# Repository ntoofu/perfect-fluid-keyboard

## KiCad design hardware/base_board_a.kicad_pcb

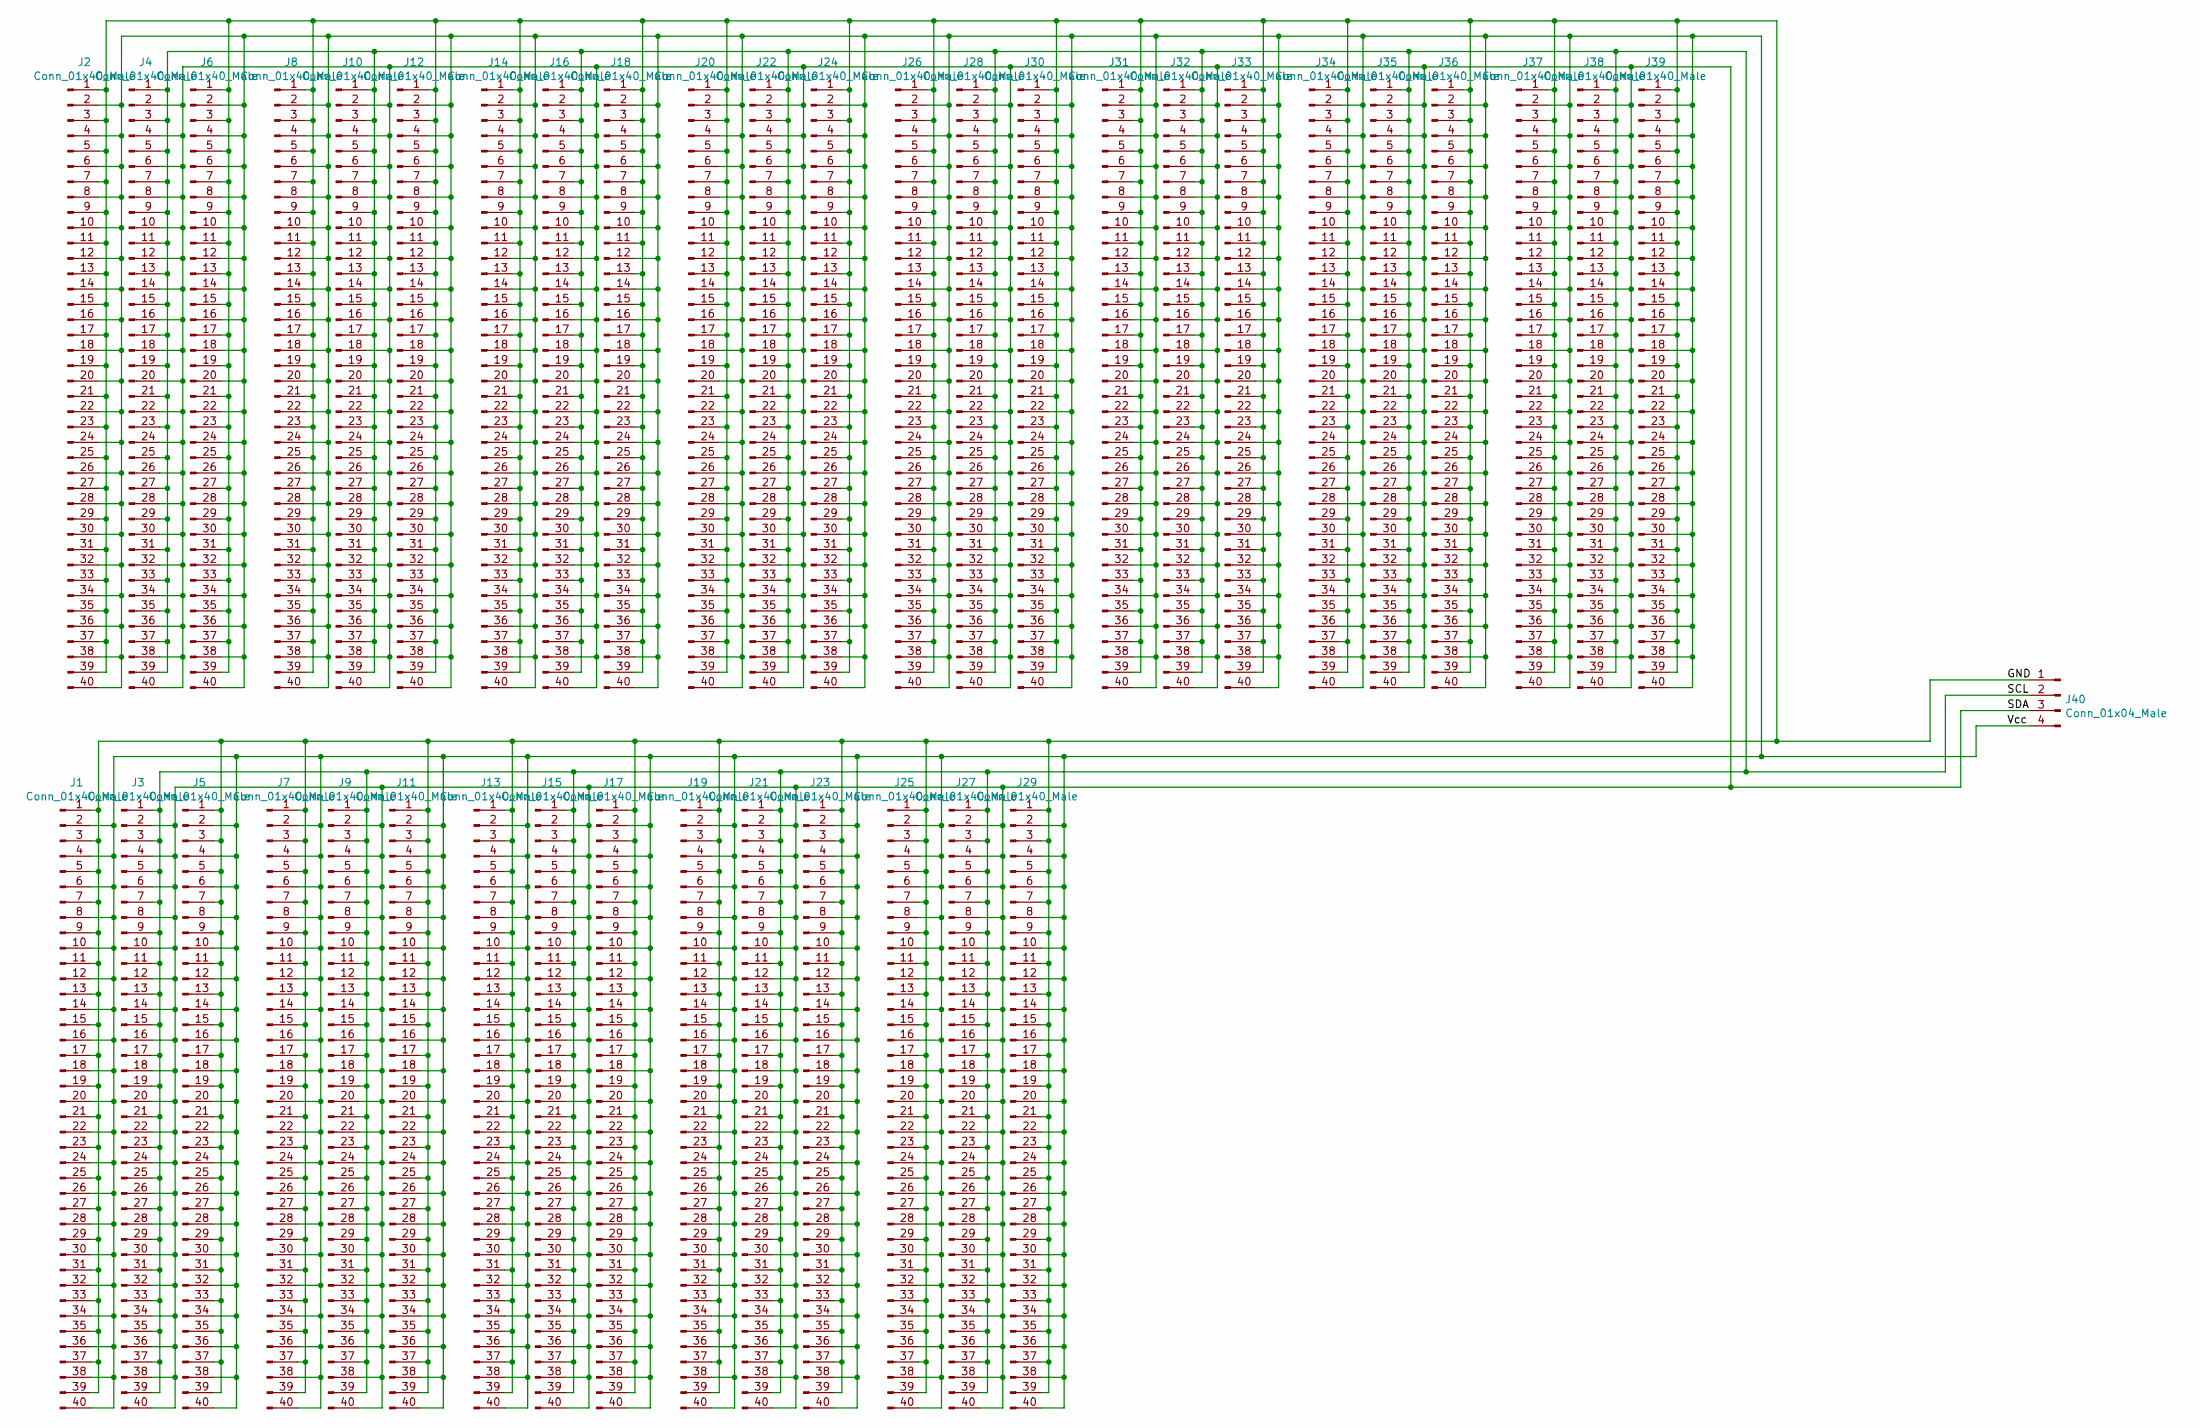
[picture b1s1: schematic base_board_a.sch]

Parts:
J1, J2, J3, J4, J5, J6, J7, J8, J9, J10, J11, J12, J13, J14, J15, J16, J17, J18, J19, J20, J21, J22, J23, J24, J25, J26, J27, J28, J29, J30, J31, J32, J33, J34, J35, J36, J37, J38, J39: Conn_01x40_Male; PinHeader_1x40_P2.54mm_Vertical
J40: Conn_01x04_Male; PinHeader_1x04_P2.54mm_Horizontal

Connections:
/GND: J1.1, J1.3, J1.5, J1.7, J1.9, J1.11, J1.13, J1.15, J1.17, J1.19, J1.21, J1.23, J1.25, J1.27, J1.29, J1.31, J1.33, J1.35, J1.37, J1.39, J2.1, J2.3, J2.5, J2.7, J2.9, J2.11, J2.13, J2.15, J2.17, J2.19, J2.21, J2.23, J2.25, J2.27, J2.29, J2.31, J2.33, J2.35, J2.37, J2.39, J5.1, J5.3, J5.5, J5.7, J5.9, J5.11, J5.13, J5.15, J5.17, J5.19, J5.21, J5.23, J5.25, J5.27, J5.29, J5.31, J5.33, J5.35, J5.37, J5.39, J6.1, J6.3, J6.5, J6.7, J6.9, J6.11, J6.13, J6.15, J6.17, J6.19, J6.21, J6.23, J6.25, J6.27, J6.29, J6.31, J6.33, J6.35, J6.37, J6.39, J7.1, J7.3, J7.5, J7.7, J7.9, J7.11, J7.13, J7.15, J7.17, J7.19, J7.21, J7.23, J7.25, J7.27, J7.29, J7.31, J7.33, J7.35, J7.37, J7.39, J8.1, J8.3, J8.5, J8.7, J8.9, J8.11, J8.13, J8.15, J8.17, J8.19, J8.21, J8.23, J8.25, J8.27, J8.29, J8.31, J8.33, J8.35, J8.37, J8.39, J11.1, J11.3, J11.5, J11.7, J11.9, J11.11, J11.13, J11.15, J11.17, J11.19, J11.21, J11.23, J11.25, J11.27, J11.29, J11.31, J11.33, J11.35, J11.37, J11.39, J12.1, J12.3, J12.5, J12.7, J12.9, J12.11, J12.13, J12.15, J12.17, J12.19, J12.21, J12.23, J12.25, J12.27, J12.29, J12.31, J12.33, J12.35, J12.37, J12.39, J13.1, J13.3, J13.5, J13.7, J13.9, J13.11, J13.13, J13.15, J13.17, J13.19, J13.21, J13.23, J13.25, J13.27, J13.29, J13.31, J13.33, J13.35, J13.37, J13.39, J14.1, J14.3, J14.5, J14.7, J14.9, J14.11, J14.13, J14.15, J14.17, J14.19, J14.21, J14.23, J14.25, J14.27, J14.29, J14.31, J14.33, J14.35, J14.37, J14.39, J17.1, J17.3, J17.5, J17.7, J17.9, J17.11, J17.13, J17.15, J17.17, J17.19, J17.21, J17.23, J17.25, J17.27, J17.29, J17.31, J17.33, J17.35, J17.37, J17.39, J18.1, J18.3, J18.5, J18.7, J18.9, J18.11, J18.13, J18.15, J18.17, J18.19, J18.21, J18.23, J18.25, J18.27, J18.29, J18.31, J18.33, J18.35, J18.37, J18.39, J19.1, J19.3, J19.5, J19.7, J19.9, J19.11, J19.13, J19.15, J19.17, J19.19, J19.21, J19.23, J19.25, J19.27, J19.29, J19.31, J19.33, J19.35, J19.37, J19.39, J20.1, J20.3, J20.5, J20.7, J20.9, J20.11, J20.13, J20.15, J20.17, J20.19, J20.21, J20.23, J20.25, J20.27, J20.29, J20.31, J20.33, J20.35, J20.37, J20.39, J23.1, J23.3, J23.5, J23.7, J23.9, J23.11, J23.13, J23.15, J23.17, J23.19, J23.21, J23.23, J23.25, J23.27, J23.29, J23.31, J23.33, J23.35, J23.37, J23.39, J24.1, J24.3, J24.5, J24.7, J24.9, J24.11, J24.13, J24.15, J24.17, J24.19, J24.21, J24.23, J24.25, J24.27, J24.29, J24.31, J24.33, J24.35, J24.37, J24.39, J25.1, J25.3, J25.5, J25.7, J25.9, J25.11, J25.13, J25.15, J25.17, J25.19, J25.21, J25.23, J25.25, J25.27, J25.29, J25.31, J25.33, J25.35, J25.37, J25.39, J26.1, J26.3, J26.5, J26.7, J26.9, J26.11, J26.13, J26.15, J26.17, J26.19, J26.21, J26.23, J26.25, J26.27, J26.29, J26.31, J26.33, J26.35, J26.37, J26.39, J29.1, J29.3, J29.5, J29.7, J29.9, J29.11, J29.13, J29.15, J29.17, J29.19, J29.21, J29.23, J29.25, J29.27, J29.29, J29.31, J29.33, J29.35, J29.37, J29.39, J30.1, J30.3, J30.5, J30.7, J30.9, J30.11, J30.13, J30.15, J30.17, J30.19, J30.21, J30.23, J30.25, J30.27, J30.29, J30.31, J30.33, J30.35, J30.37, J30.39, J31.1, J31.3, J31.5, J31.7, J31.9, J31.11, J31.13, J31.15, J31.17, J31.19, J31.21, J31.23, J31.25, J31.27, J31.29, J31.31, J31.33, J31.35, J31.37, J31.39, J33.1, J33.3, J33.5, J33.7, J33.9, J33.11, J33.13, J33.15, J33.17, J33.19, J33.21, J33.23, J33.25, J33.27, J33.29, J33.31, J33.33, J33.35, J33.37, J33.39, J34.1, J34.3, J34.5, J34.7, J34.9, J34.11, J34.13, J34.15, J34.17, J34.19, J34.21, J34.23, J34.25, J34.27, J34.29, J34.31, J34.33, J34.35, J34.37, J34.39, J36.1, J36.3, J36.5, J36.7, J36.9, J36.11, J36.13, J36.15, J36.17, J36.19, J36.21, J36.23, J36.25, J36.27, J36.29, J36.31, J36.33, J36.35, J36.37, J36.39, J37.1, J37.3, J37.5, J37.7, J37.9, J37.11, J37.13, J37.15, J37.17, J37.19, J37.21, J37.23, J37.25, J37.27, J37.29, J37.31, J37.33, J37.35, J37.37, J37.39, J39.1, J39.3, J39.5, J39.7, J39.9, J39.11, J39.13, J39.15, J39.17, J39.19, J39.21, J39.23, J39.25, J39.27, J39.29, J39.31, J39.33, J39.35, J39.37, J39.39, J40.1
/SCL: J3.1, J3.3, J3.5, J3.7, J3.9, J3.11, J3.13, J3.15, J3.17, J3.19, J3.21, J3.23, J3.25, J3.27, J3.29, J3.31, J3.33, J3.35, J3.37, J3.39, J4.1, J4.3, J4.5, J4.7, J4.9, J4.11, J4.13, J4.15, J4.17, J4.19, J4.21, J4.23, J4.25, J4.27, J4.29, J4.31, J4.33, J4.35, J4.37, J4.39, J9.1, J9.3, J9.5, J9.7, J9.9, J9.11, J9.13, J9.15, J9.17, J9.19, J9.21, J9.23, J9.25, J9.27, J9.29, J9.31, J9.33, J9.35, J9.37, J9.39, J10.1, J10.3, J10.5, J10.7, J10.9, J10.11, J10.13, J10.15, J10.17, J10.19, J10.21, J10.23, J10.25, J10.27, J10.29, J10.31, J10.33, J10.35, J10.37, J10.39, J15.1, J15.3, J15.5, J15.7, J15.9, J15.11, J15.13, J15.15, J15.17, J15.19, J15.21, J15.23, J15.25, J15.27, J15.29, J15.31, J15.33, J15.35, J15.37, J15.39, J16.1, J16.3, J16.5, J16.7, J16.9, J16.11, J16.13, J16.15, J16.17, J16.19, J16.21, J16.23, J16.25, J16.27, J16.29, J16.31, J16.33, J16.35, J16.37, J16.39, J21.1, J21.3, J21.5, J21.7, J21.9, J21.11, J21.13, J21.15, J21.17, J21.19, J21.21, J21.23, J21.25, J21.27, J21.29, J21.31, J21.33, J21.35, J21.37, J21.39, J22.1, J22.3, J22.5, J22.7, J22.9, J22.11, J22.13, J22.15, J22.17, J22.19, J22.21, J22.23, J22.25, J22.27, J22.29, J22.31, J22.33, J22.35, J22.37, J22.39, J27.1, J27.3, J27.5, J27.7, J27.9, J27.11, J27.13, J27.15, J27.17, J27.19, J27.21, J27.23, J27.25, J27.27, J27.29, J27.31, J27.33, J27.35, J27.37, J27.39, J28.1, J28.3, J28.5, J28.7, J28.9, J28.11, J28.13, J28.15, J28.17, J28.19, J28.21, J28.23, J28.25, J28.27, J28.29, J28.31, J28.33, J28.35, J28.37, J28.39, J32.1, J32.3, J32.5, J32.7, J32.9, J32.11, J32.13, J32.15, J32.17, J32.19, J32.21, J32.23, J32.25, J32.27, J32.29, J32.31, J32.33, J32.35, J32.37, J32.39, J35.1, J35.3, J35.5, J35.7, J35.9, J35.11, J35.13, J35.15, J35.17, J35.19, J35.21, J35.23, J35.25, J35.27, J35.29, J35.31, J35.33, J35.35, J35.37, J35.39, J38.1, J38.3, J38.5, J38.7, J38.9, J38.11, J38.13, J38.15, J38.17, J38.19, J38.21, J38.23, J38.25, J38.27, J38.29, J38.31, J38.33, J38.35, J38.37, J38.39, J40.2
/SDA: J3.2, J3.4, J3.6, J3.8, J3.10, J3.12, J3.14, J3.16, J3.18, J3.20, J3.22, J3.24, J3.26, J3.28, J3.30, J3.32, J3.34, J3.36, J3.38, J3.40, J4.2, J4.4, J4.6, J4.8, J4.10, J4.12, J4.14, J4.16, J4.18, J4.20, J4.22, J4.24, J4.26, J4.28, J4.30, J4.32, J4.34, J4.36, J4.38, J4.40, J9.2, J9.4, J9.6, J9.8, J9.10, J9.12, J9.14, J9.16, J9.18, J9.20, J9.22, J9.24, J9.26, J9.28, J9.30, J9.32, J9.34, J9.36, J9.38, J9.40, J10.2, J10.4, J10.6, J10.8, J10.10, J10.12, J10.14, J10.16, J10.18, J10.20, J10.22, J10.24, J10.26, J10.28, J10.30, J10.32, J10.34, J10.36, J10.38, J10.40, J15.2, J15.4, J15.6, J15.8, J15.10, J15.12, J15.14, J15.16, J15.18, J15.20, J15.22, J15.24, J15.26, J15.28, J15.30, J15.32, J15.34, J15.36, J15.38, J15.40, J16.2, J16.4, J16.6, J16.8, J16.10, J16.12, J16.14, J16.16, J16.18, J16.20, J16.22, J16.24, J16.26, J16.28, J16.30, J16.32, J16.34, J16.36, J16.38, J16.40, J21.2, J21.4, J21.6, J21.8, J21.10, J21.12, J21.14, J21.16, J21.18, J21.20, J21.22, J21.24, J21.26, J21.28, J21.30, J21.32, J21.34, J21.36, J21.38, J21.40, J22.2, J22.4, J22.6, J22.8, J22.10, J22.12, J22.14, J22.16, J22.18, J22.20, J22.22, J22.24, J22.26, J22.28, J22.30, J22.32, J22.34, J22.36, J22.38, J22.40, J27.2, J27.4, J27.6, J27.8, J27.10, J27.12, J27.14, J27.16, J27.18, J27.20, J27.22, J27.24, J27.26, J27.28, J27.30, J27.32, J27.34, J27.36, J27.38, J27.40, J28.2, J28.4, J28.6, J28.8, J28.10, J28.12, J28.14, J28.16, J28.18, J28.20, J28.22, J28.24, J28.26, J28.28, J28.30, J28.32, J28.34, J28.36, J28.38, J28.40, J32.2, J32.4, J32.6, J32.8, J32.10, J32.12, J32.14, J32.16, J32.18, J32.20, J32.22, J32.24, J32.26, J32.28, J32.30, J32.32, J32.34, J32.36, J32.38, J32.40, J35.2, J35.4, J35.6, J35.8, J35.10, J35.12, J35.14, J35.16, J35.18, J35.20, J35.22, J35.24, J35.26, J35.28, J35.30, J35.32, J35.34, J35.36, J35.38, J35.40, J38.2, J38.4, J38.6, J38.8, J38.10, J38.12, J38.14, J38.16, J38.18, J38.20, J38.22, J38.24, J38.26, J38.28, J38.30, J38.32, J38.34, J38.36, J38.38, J38.40, J40.3
/Vcc: J1.2, J1.4, J1.6, J1.8, J1.10, J1.12, J1.14, J1.16, J1.18, J1.20, J1.22, J1.24, J1.26, J1.28, J1.30, J1.32, J1.34, J1.36, J1.38, J1.40, J2.2, J2.4, J2.6, J2.8, J2.10, J2.12, J2.14, J2.16, J2.18, J2.20, J2.22, J2.24, J2.26, J2.28, J2.30, J2.32, J2.34, J2.36, J2.38, J2.40, J5.2, J5.4, J5.6, J5.8, J5.10, J5.12, J5.14, J5.16, J5.18, J5.20, J5.22, J5.24, J5.26, J5.28, J5.30, J5.32, J5.34, J5.36, J5.38, J5.40, J6.2, J6.4, J6.6, J6.8, J6.10, J6.12, J6.14, J6.16, J6.18, J6.20, J6.22, J6.24, J6.26, J6.28, J6.30, J6.32, J6.34, J6.36, J6.38, J6.40, J7.2, J7.4, J7.6, J7.8, J7.10, J7.12, J7.14, J7.16, J7.18, J7.20, J7.22, J7.24, J7.26, J7.28, J7.30, J7.32, J7.34, J7.36, J7.38, J7.40, J8.2, J8.4, J8.6, J8.8, J8.10, J8.12, J8.14, J8.16, J8.18, J8.20, J8.22, J8.24, J8.26, J8.28, J8.30, J8.32, J8.34, J8.36, J8.38, J8.40, J11.2, J11.4, J11.6, J11.8, J11.10, J11.12, J11.14, J11.16, J11.18, J11.20, J11.22, J11.24, J11.26, J11.28, J11.30, J11.32, J11.34, J11.36, J11.38, J11.40, J12.2, J12.4, J12.6, J12.8, J12.10, J12.12, J12.14, J12.16, J12.18, J12.20, J12.22, J12.24, J12.26, J12.28, J12.30, J12.32, J12.34, J12.36, J12.38, J12.40, J13.2, J13.4, J13.6, J13.8, J13.10, J13.12, J13.14, J13.16, J13.18, J13.20, J13.22, J13.24, J13.26, J13.28, J13.30, J13.32, J13.34, J13.36, J13.38, J13.40, J14.2, J14.4, J14.6, J14.8, J14.10, J14.12, J14.14, J14.16, J14.18, J14.20, J14.22, J14.24, J14.26, J14.28, J14.30, J14.32, J14.34, J14.36, J14.38, J14.40, J17.2, J17.4, J17.6, J17.8, J17.10, J17.12, J17.14, J17.16, J17.18, J17.20, J17.22, J17.24, J17.26, J17.28, J17.30, J17.32, J17.34, J17.36, J17.38, J17.40, J18.2, J18.4, J18.6, J18.8, J18.10, J18.12, J18.14, J18.16, J18.18, J18.20, J18.22, J18.24, J18.26, J18.28, J18.30, J18.32, J18.34, J18.36, J18.38, J18.40, J19.2, J19.4, J19.6, J19.8, J19.10, J19.12, J19.14, J19.16, J19.18, J19.20, J19.22, J19.24, J19.26, J19.28, J19.30, J19.32, J19.34, J19.36, J19.38, J19.40, J20.2, J20.4, J20.6, J20.8, J20.10, J20.12, J20.14, J20.16, J20.18, J20.20, J20.22, J20.24, J20.26, J20.28, J20.30, J20.32, J20.34, J20.36, J20.38, J20.40, J23.2, J23.4, J23.6, J23.8, J23.10, J23.12, J23.14, J23.16, J23.18, J23.20, J23.22, J23.24, J23.26, J23.28, J23.30, J23.32, J23.34, J23.36, J23.38, J23.40, J24.2, J24.4, J24.6, J24.8, J24.10, J24.12, J24.14, J24.16, J24.18, J24.20, J24.22, J24.24, J24.26, J24.28, J24.30, J24.32, J24.34, J24.36, J24.38, J24.40, J25.2, J25.4, J25.6, J25.8, J25.10, J25.12, J25.14, J25.16, J25.18, J25.20, J25.22, J25.24, J25.26, J25.28, J25.30, J25.32, J25.34, J25.36, J25.38, J25.40, J26.2, J26.4, J26.6, J26.8, J26.10, J26.12, J26.14, J26.16, J26.18, J26.20, J26.22, J26.24, J26.26, J26.28, J26.30, J26.32, J26.34, J26.36, J26.38, J26.40, J29.2, J29.4, J29.6, J29.8, J29.10, J29.12, J29.14, J29.16, J29.18, J29.20, J29.22, J29.24, J29.26, J29.28, J29.30, J29.32, J29.34, J29.36, J29.38, J29.40, J30.2, J30.4, J30.6, J30.8, J30.10, J30.12, J30.14, J30.16, J30.18, J30.20, J30.22, J30.24, J30.26, J30.28, J30.30, J30.32, J30.34, J30.36, J30.38, J30.40, J31.2, J31.4, J31.6, J31.8, J31.10, J31.12, J31.14, J31.16, J31.18, J31.20, J31.22, J31.24, J31.26, J31.28, J31.30, J31.32, J31.34, J31.36, J31.38, J31.40, J33.2, J33.4, J33.6, J33.8, J33.10, J33.12, J33.14, J33.16, J33.18, J33.20, J33.22, J33.24, J33.26, J33.28, J33.30, J33.32, J33.34, J33.36, J33.38, J33.40, J34.2, J34.4, J34.6, J34.8, J34.10, J34.12, J34.14, J34.16, J34.18, J34.20, J34.22, J34.24, J34.26, J34.28, J34.30, J34.32, J34.34, J34.36, J34.38, J34.40, J36.2, J36.4, J36.6, J36.8, J36.10, J36.12, J36.14, J36.16, J36.18, J36.20, J36.22, J36.24, J36.26, J36.28, J36.30, J36.32, J36.34, J36.36, J36.38, J36.40, J37.2, J37.4, J37.6, J37.8, J37.10, J37.12, J37.14, J37.16, J37.18, J37.20, J37.22, J37.24, J37.26, J37.28, J37.30, J37.32, J37.34, J37.36, J37.38, J37.40, J39.2, J39.4, J39.6, J39.8, J39.10, J39.12, J39.14, J39.16, J39.18, J39.20, J39.22, J39.24, J39.26, J39.28, J39.30, J39.32, J39.34, J39.36, J39.38, J39.40, J40.4

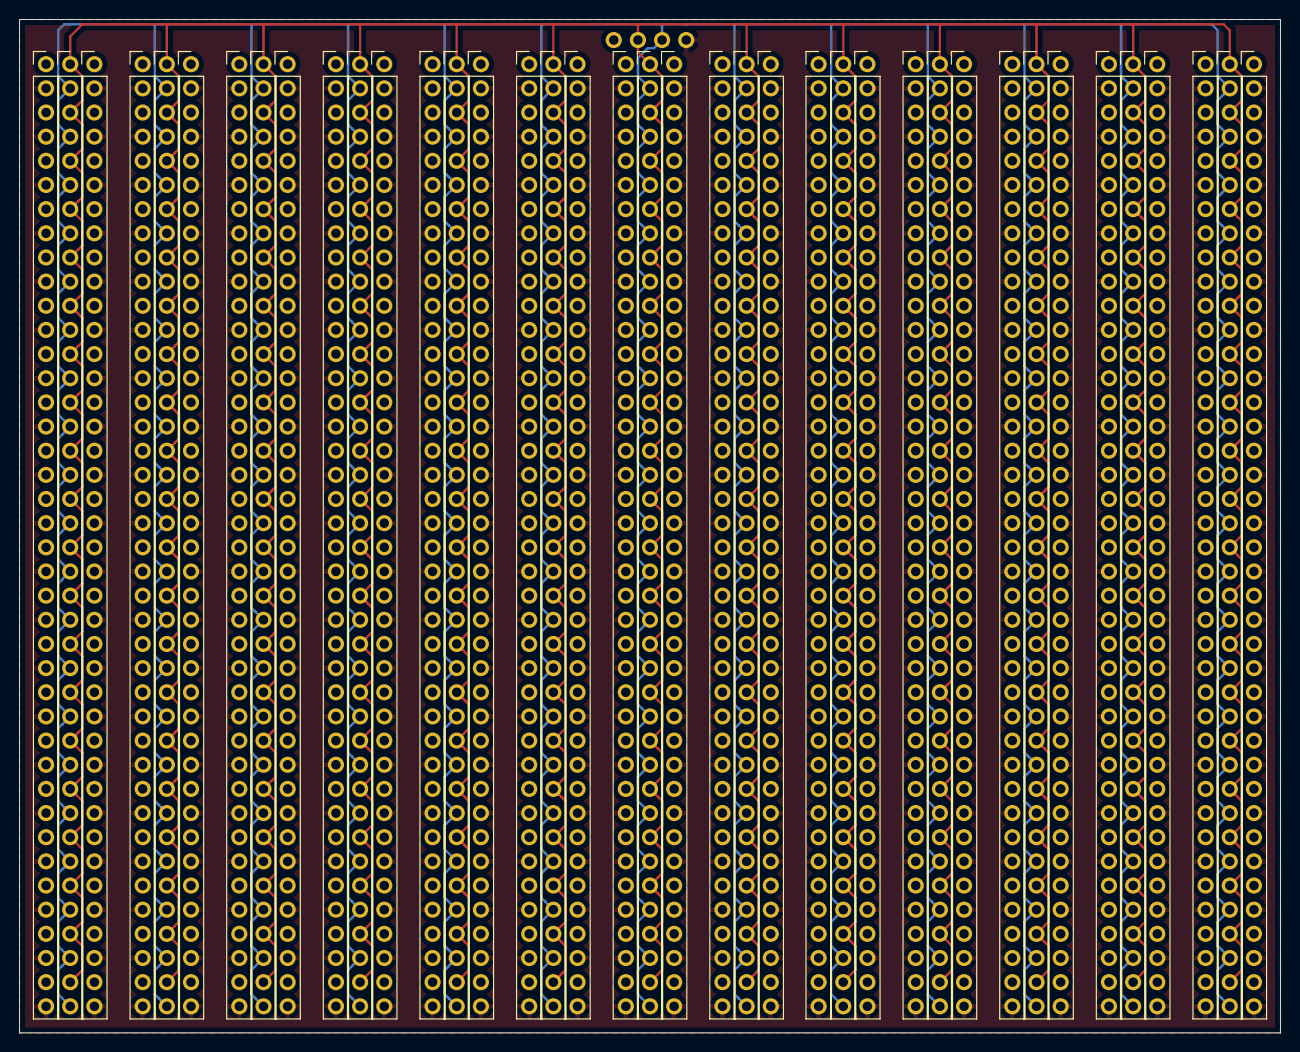
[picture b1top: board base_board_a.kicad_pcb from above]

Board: 2 copper layers, 132.6 x 106.6 mm, 40 parts (0 on the bottom side), 4 nets.

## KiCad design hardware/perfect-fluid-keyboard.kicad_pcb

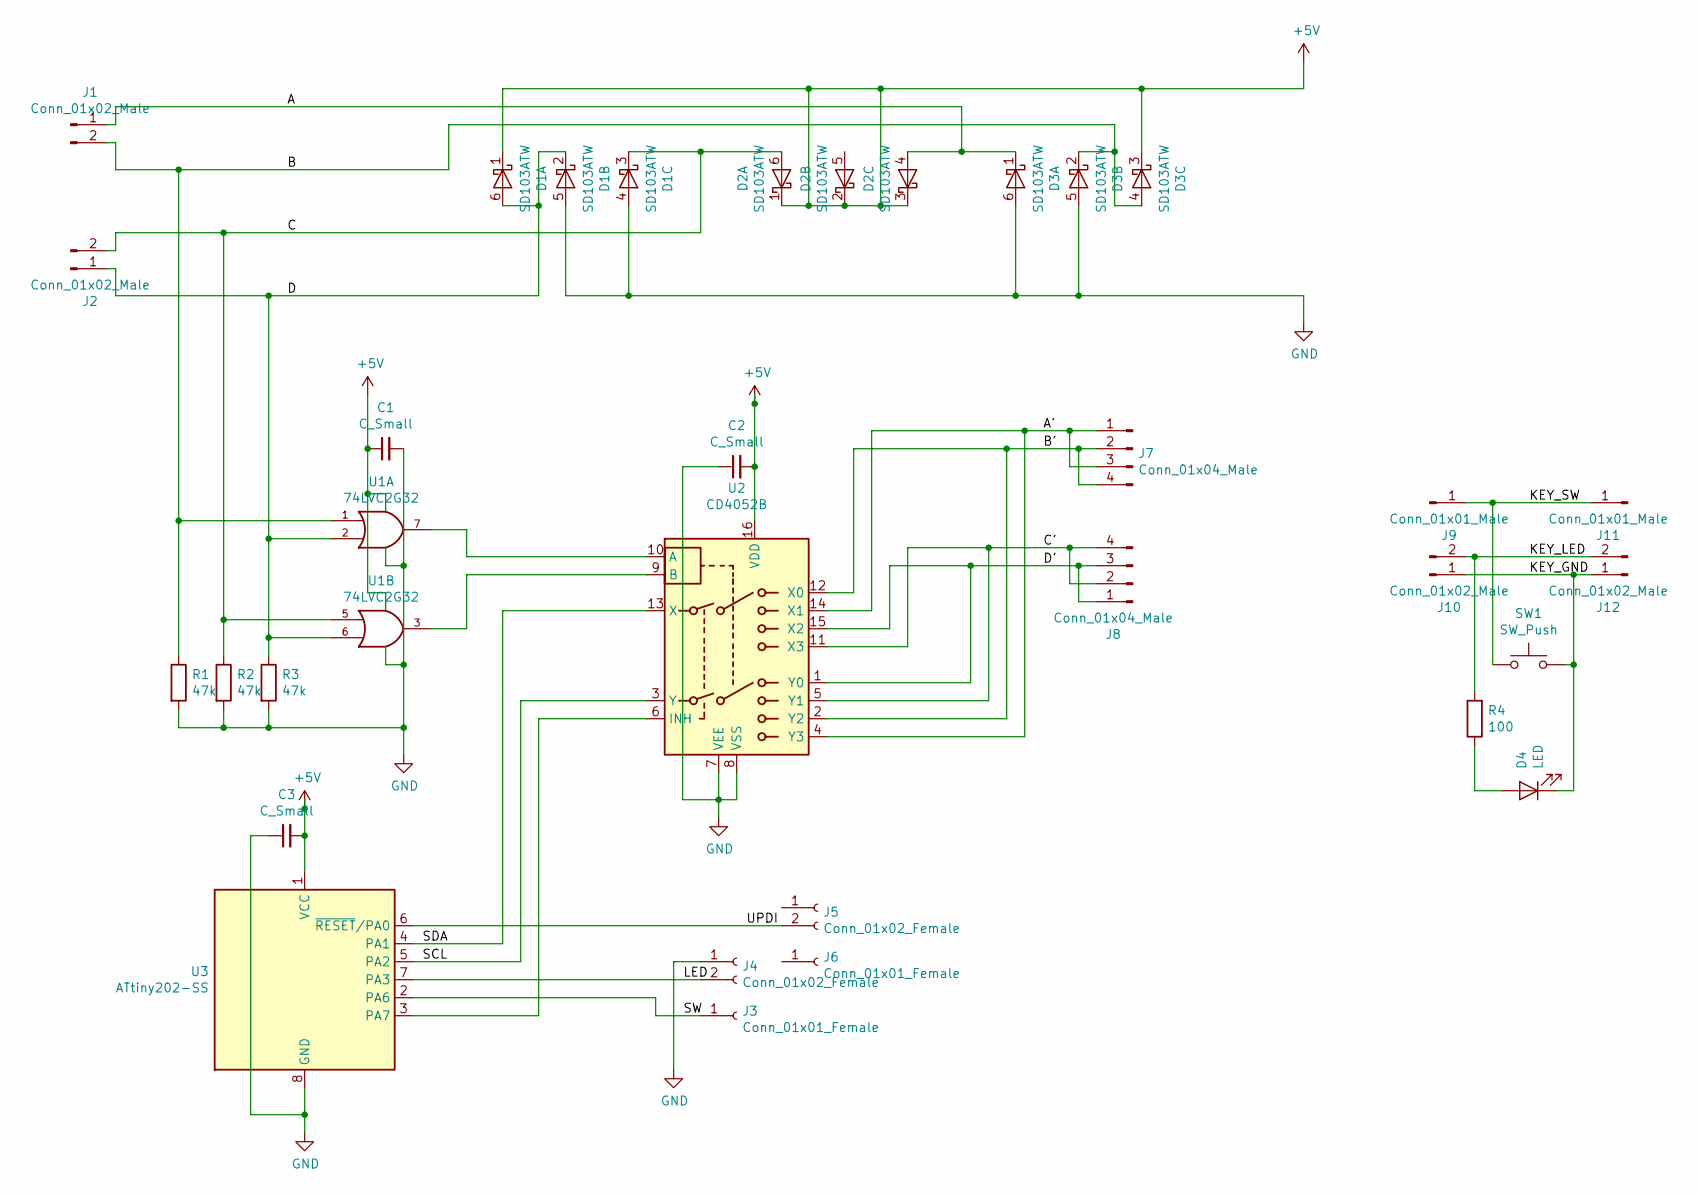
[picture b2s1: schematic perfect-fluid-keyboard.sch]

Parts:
C1, C2, C3: C_Small; C_0603_1608Metric_Pad1.05x0.95mm_HandSolder
D1, D2, D3: SD103ATW; SOT-363_SC-70-6
D4: LED; LED_D3.0mm
J1, J2, J10, J12: Conn_01x02_Male; PinHeader_1x02_P2.54mm_Vertical
J3, J6: Conn_01x01_Female; PinSocket_1x01_P2.54mm_Vertical
J4, J5: Conn_01x02_Female; PinSocket_1x02_P2.54mm_Vertical
J7, J8: Conn_01x04_Male; PinHeader_1x04_P2.54mm_Vertical
J9, J11: Conn_01x01_Male; PinHeader_1x01_P2.54mm_Vertical
R1, R2, R3: 47k; R_0603_1608Metric_Pad1.05x0.95mm_HandSolder
R4: 100; R_0603_1608Metric_Pad1.05x0.95mm_HandSolder
SW1: SW_Push; SW_Cherry_MX_1.00u_PCB
U1: 74LVC2G32; SSOP-8_2.95x2.8mm_P0.65mm
U2: CD4052B; SSOP-16_5.3x6.2mm_P0.65mm
U3: ATtiny202-SS; SOIC-8_3.9x4.9mm_P1.27mm

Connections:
+5V: C1.1, C2.2, C3.2, D1.1 (K), D2.1 (K), D2.2 (K), D2.3 (K), D3.3 (K), U1.8 (VCC), U2.16 (VDD), U3.1 (VCC)
/A: D2.4 (A), D3.1 (K), J1.1
/A': J7.1, J7.3, U2.4 (Y3), U2.14 (X1)
/B: D3.2 (K), D3.4 (A), J1.2, R1.1, U1.1
/B': J7.2, J7.4, U2.2 (Y2), U2.12 (X0)
/C: D1.3 (K), D2.6 (A), J2.2, R2.1, U1.5
/C': J8.2, J8.4, U2.5 (Y1), U2.11 (X3)
/D: D1.2 (K), D1.6 (A), J2.1, R3.1, U1.2, U1.6
/D': J8.1, J8.3, U2.1 (Y0), U2.15 (X2)
/KEY_GND: D4.1 (K), J10.1, J12.1, SW1.1
/KEY_LED: J10.2, J12.2, R4.2
/KEY_SW: J9.1, J11.1, SW1.2
/LED: J4.2, U3.7 (PA3)
/SCL: U2.3 (Y), U3.5 (PA2)
/SDA: U2.13 (X), U3.4 (PA1)
/SW: J3.1, U3.2 (PA6)
/UPDI: J5.2, U3.6 (~RESET~/PA0)
GND: C1.2, C2.1, C3.1, D1.4 (A), D1.5 (A), D3.5 (A), D3.6 (A), J4.1, R1.2, R2.2, R3.2, U1.4 (GND), U2.7 (VEE), U2.8 (VSS), U3.8 (GND)
unnamed: D4.2 (A), R4.1
unnamed: U1.3, U2.9 (B)
unnamed: U1.7, U2.10 (A)
unnamed: U2.6 (INH), U3.3 (PA7)

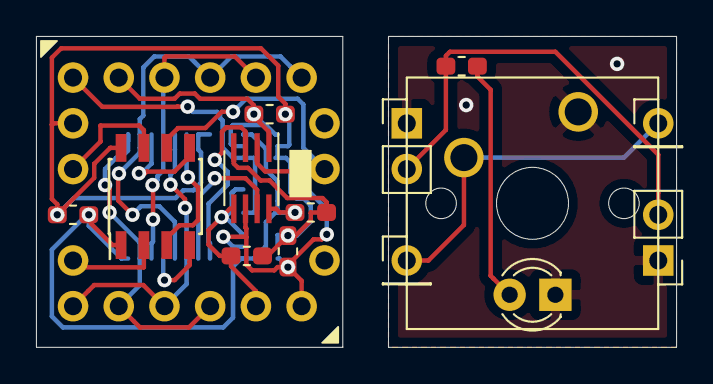
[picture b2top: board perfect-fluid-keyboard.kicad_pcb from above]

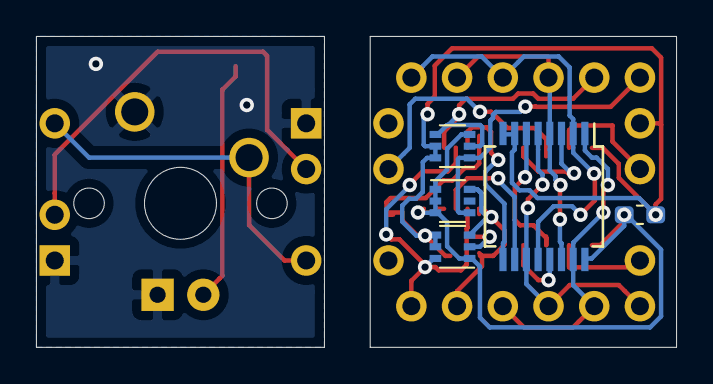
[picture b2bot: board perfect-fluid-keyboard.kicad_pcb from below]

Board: 2 copper layers, 35.6 x 17.3 mm, 27 parts (9 on the bottom side), 22 nets.

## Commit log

2019-09-18 Initial commit (under development)
2019-09-23 Add files for reproducible builds
2019-10-06 Fix Makefile
2019-10-13 Load I2C address from EEPROM
    to use the same program ihex file (`key-controller.hex`) among keys.
    Key ID, which is an integer between 0 and 111, is written to EEPROM by using SQTP file (`key_id_sqtp.num`)
2019-12-07 Update QMK firmware version
2019-12-07 Add built image of firmware for keys
